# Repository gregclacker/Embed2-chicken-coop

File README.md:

# Embed2 chicken coop
bawk bawk box

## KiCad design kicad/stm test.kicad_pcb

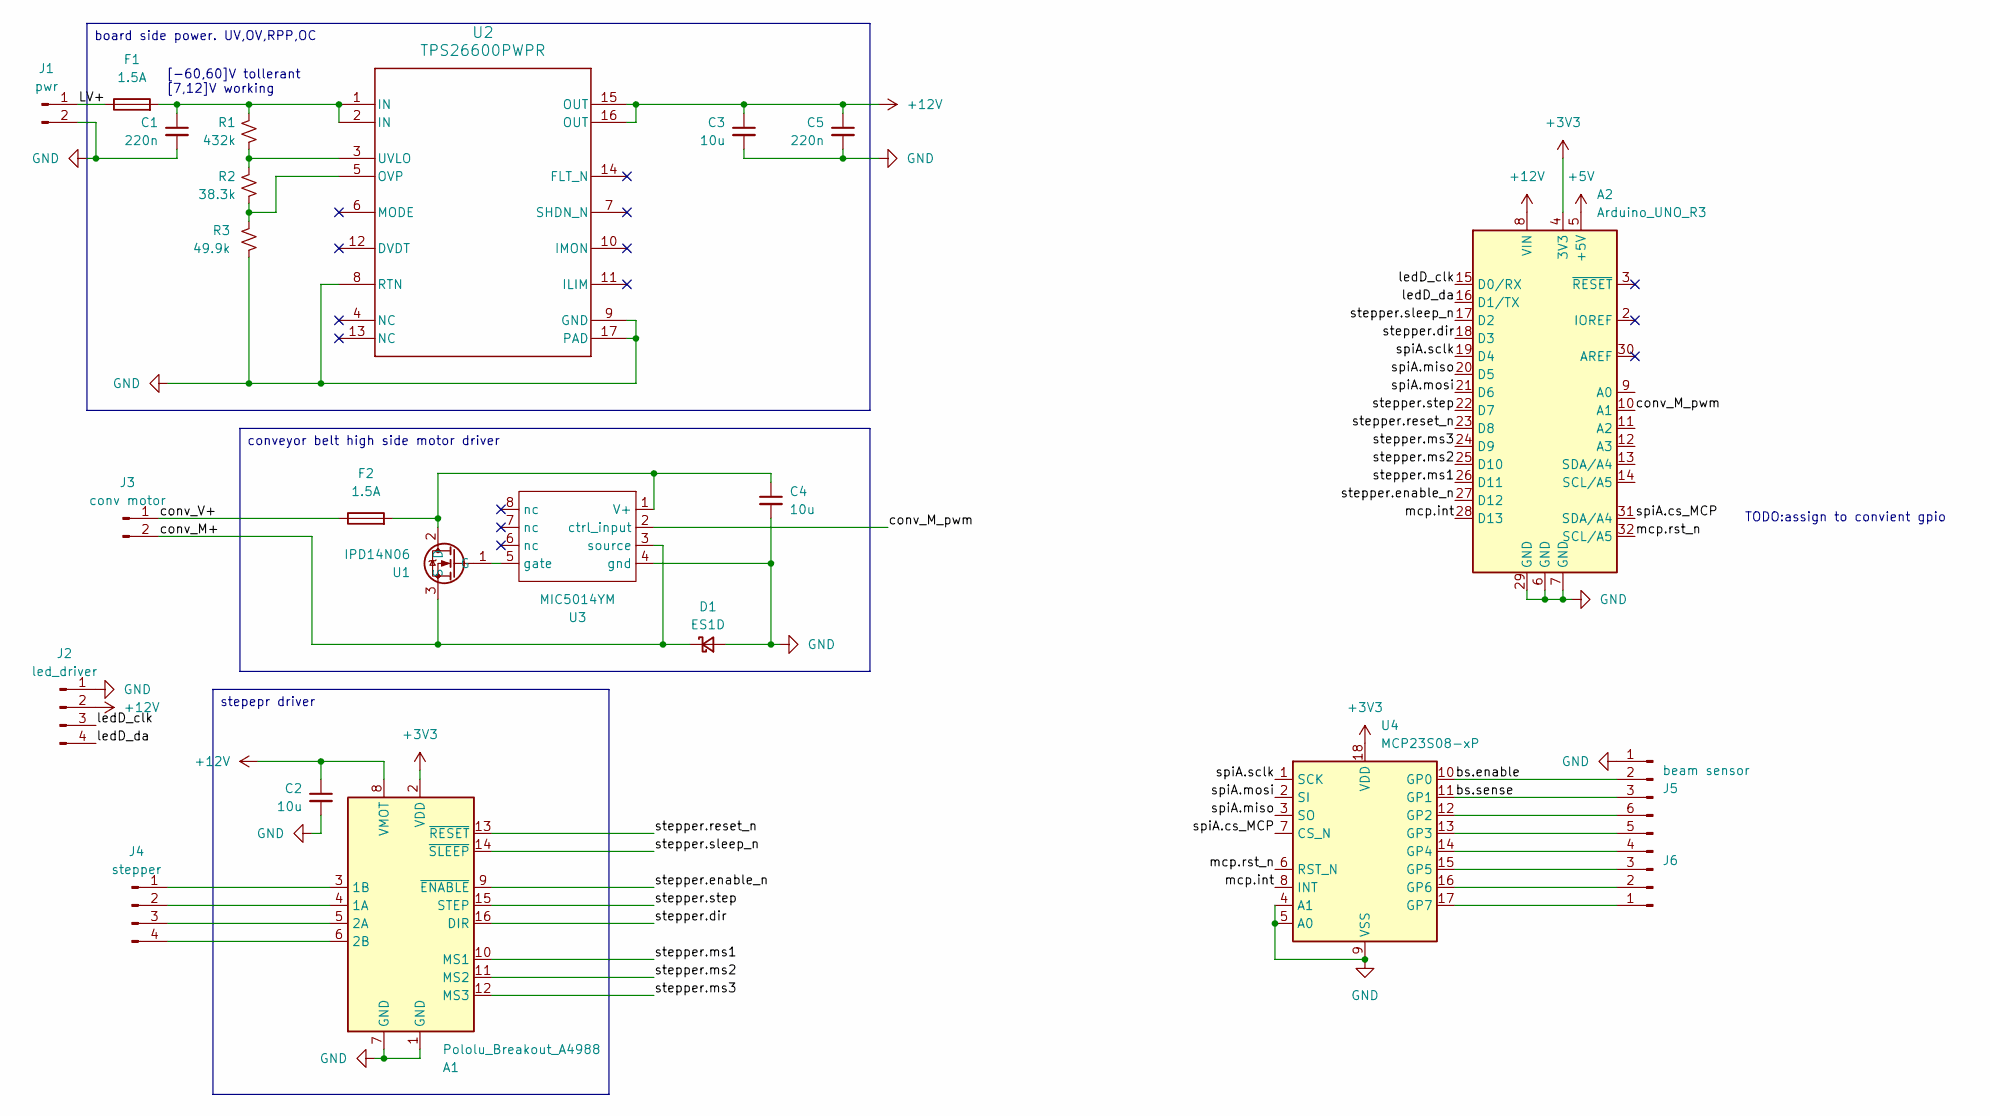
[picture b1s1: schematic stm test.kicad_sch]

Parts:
A1: Pololu_Breakout_A4988; Pololu_Breakout-16_15.2x20.3mm
A2: Arduino_UNO_R3
C1, C5: 220n; C_0805_2012Metric_Pad1.18x1.45mm_HandSolder
C2, C3, C4: 10u; C_1206_3216Metric_Pad1.33x1.80mm_HandSolder
D1: ES1D; D_SMA
F1, F2: 1.5A; R_Axial_DIN0207_L6.3mm_D2.5mm_P7.62mm_Horizontal
J1: pwr; TerminalBlock_Xinya_XY308-2.54-2P_1x02_P2.54mm_Horizontal
J2: led_driver; TerminalBlock_Xinya_XY308-2.54-4P_1x04_P2.54mm_Horizontal
J3: conv motor; TerminalBlock_Xinya_XY308-2.54-2P_1x02_P2.54mm_Horizontal
J4: stepper; TerminalBlock_Xinya_XY308-2.54-4P_1x04_P2.54mm_Horizontal
J5: beam sensor; TerminalBlock_Xinya_XY308-2.54-3P_1x03_P2.54mm_Horizontal
J6: Conn_01x06_Pin; PinHeader_1x06_P2.54mm_Vertical
R1: 432k; R_1206_3216Metric_Pad1.30x1.75mm_HandSolder
R2: 38.3k; R_0805_2012Metric_Pad1.20x1.40mm_HandSolder
R3: 49.9k; R_0805_2012Metric_Pad1.20x1.40mm_HandSolder
U1: IPD14N06; TO-252-2
U2: TPS26600PWPR; PWP0016H_M
U3: MIC5014YM; SOIC-8_3.9x4.9mm_P1.27mm
U4: MCP23S08-xP; DIP-18_W7.62mm

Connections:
+3V3: A1.2 (VDD), A2.4 (3V3), U4.18 (VDD)
+5V: A2.5 (+5V)
+12V: A1.8 (VMOT), A2.8 (VIN), C2.1, C3.1, C5.1, J2.2, U2.15 (OUT), U2.16 (OUT)
/LV+: F1.1, J1.1
/bs.enable: J5.2, U4.10 (GP0)
/bs.sense: J5.3, U4.11 (GP1)
/conv_M+: D1.1 (K), J3.2, U1.3 (S), U3.3 (source)
/conv_M_pwm: A2.10 (A1), U3.2 (ctrl_input)
/conv_V+: F2.1, J3.1
/ledD_clk: A2.15 (D0/RX), J2.3
/ledD_da: A2.16 (D1/TX), J2.4
/mcp.int: A2.28 (D13), U4.8 (INT)
/mcp.rst_n: A2.32 (SCL/A5), U4.6 (RST_N)
/spiA.cs_MCP: A2.31 (SDA/A4), U4.7 (CS_N)
/spiA.miso: A2.20 (D5), U4.3 (SO)
/spiA.mosi: A2.21 (D6), U4.2 (SI)
/spiA.sclk: A2.19 (D4), U4.1 (SCK)
/stepper.dir: A1.16 (DIR), A2.18 (D3)
/stepper.enable_n: A1.9 (~ENABLE), A2.27 (D12)
/stepper.ms1: A1.10 (MS1), A2.26 (D11)
/stepper.ms2: A1.11 (MS2), A2.25 (D10)
/stepper.ms3: A1.12 (MS3), A2.24 (D9)
/stepper.reset_n: A1.13 (~RESET), A2.23 (D8)
/stepper.sleep_n: A1.14 (~SLEEP), A2.17 (D2)
/stepper.step: A1.15 (STEP), A2.22 (D7)
GND: A1.1 (GND), A1.7 (GND), A2.6 (GND), A2.7 (GND), A2.29 (GND), C1.2, C2.2, C3.2, C4.2, C5.2, D1.2 (A), J1.2, J2.1, J5.1, R3.1, U2.8 (RTN), U2.9 (GND), U2.17 (PAD), U3.4 (gnd), U4.4 (A1), U4.5 (A0), U4.9 (VSS)
unnamed: A1.4 (1A), J4.2
unnamed: A1.3 (1B), J4.1
unnamed: A1.5 (2A), J4.3
unnamed: A1.6 (2B), J4.4
unnamed: C1.1, F1.2, R1.2, U2.1 (IN), U2.2 (IN)
unnamed: J6.1, U4.17 (GP7)
unnamed: J6.2, U4.16 (GP6)
unnamed: J6.3, U4.15 (GP5)
unnamed: J6.4, U4.14 (GP4)
unnamed: J6.5, U4.13 (GP3)
unnamed: J6.6, U4.12 (GP2)
unnamed: C4.1, F2.2, U1.2 (D), U3.1 (V+)
unnamed: U1.1 (G), U3.5 (gate)
unnamed: R2.1, R3.2, U2.5 (OVP)
unnamed: R1.1, R2.2, U2.3 (UVLO)

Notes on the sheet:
[-60,60]V tollerant [7,12]V working
TODO:assign to convient gpio
stepepr driver
conveyor belt high side motor driver
board side power. UV,OV,RPP,OC

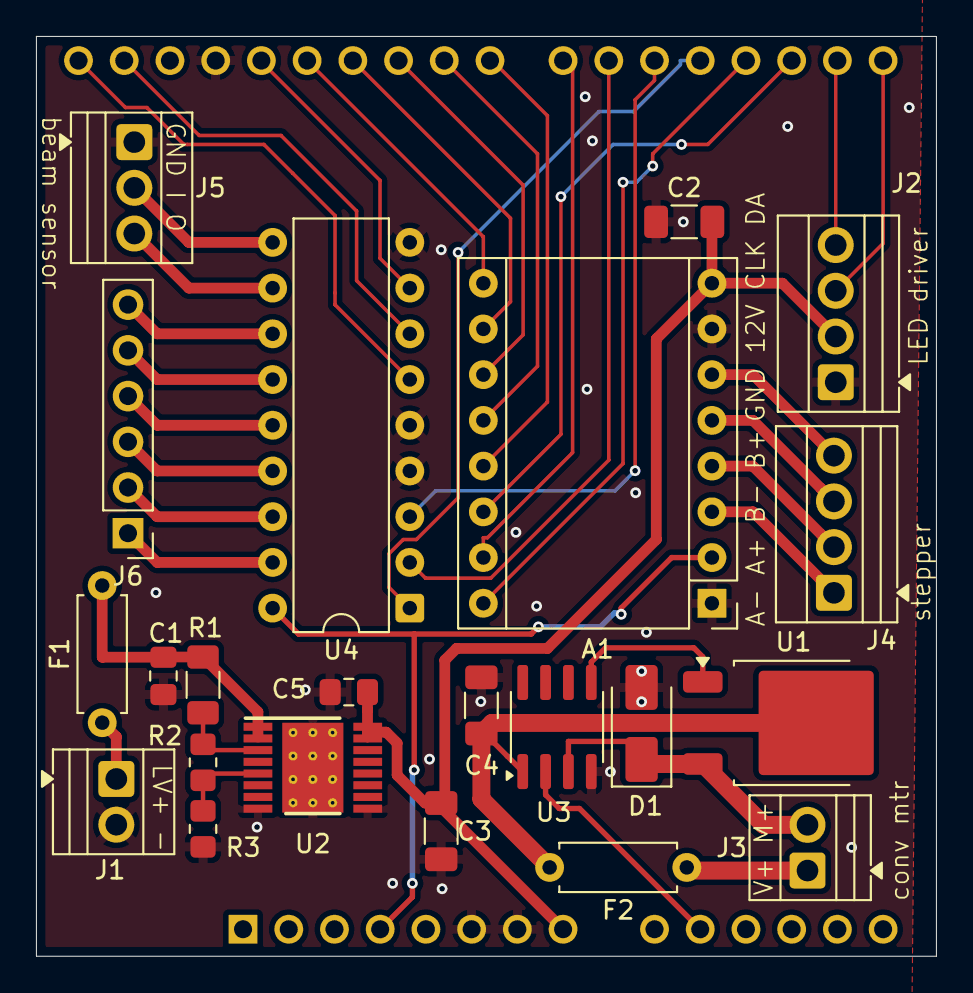
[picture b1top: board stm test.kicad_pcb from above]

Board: 2 copper layers, 50.0 x 51.1 mm, 23 parts (1 on the bottom side), 40 nets.

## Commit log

2026-03-29 wompers
2026-03-29 womp
2026-03-30 corrected spi wiring error
2026-04-01 beam sensor and conveyor belt code
2026-04-02 i fugged up
2026-04-08 test pin
2026-04-13 corrected stepper pins and led driver pins
2026-04-15 something
2026-04-15 lewkjcealnkfe
    bubmaxxing mewwow mwomcae
2026-04-17 added hall effect sensors
2026-04-19 blub
    pacenoeac
2026-04-20 tests and project files
2026-04-20 led test
2026-04-20 blug?
2026-04-20 conv works
2026-04-26 jfekjbfejkbaef
2026-04-26 gsgsgff
2026-04-26 blub
2026-04-26 ljlacekl
2026-04-26 asdasd
2026-04-26 workemn
